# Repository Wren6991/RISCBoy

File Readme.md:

RISCBoy
=======

RISCBoy is an open-source portable games console, designed from scratch. This includes:

- A RISC-V compatible CPU
- A raster graphics pipeline and display controller
- Other chip infrastructure: busfabric, memory controllers, UART, GPIO etc.
- A PCB layout in KiCad

It is a Gameboy Advance from a parallel universe where RISC-V existed in 2001. A love letter to the handheld consoles from my childhood, and a 3AM drunk text to the technology that powered them.

The design is written in synthesisable Verilog 2005, and is intended to fit onto an iCE40-HX8k FPGA. This is a LUT4-based FPGA with 7680 logic elements, so fitting a 32 bit games console requires a crowbar and some vaseline, or perhaps just careful design. The HX8k was once the largest FPGA targeted by the open-source [Icestorm](http://www.clifford.at/icestorm/) FPGA toolchain, but that toolchain has since [moved on](https://github.com/SymbiFlow/prjtrellis) to [greater things](https://github.com/SymbiFlow/prjxray).

More detailed information can be found in the [documentation](doc/riscboy_doc.pdf).

The processor supports the RV32IMC instruction set, and passes the RISC-V compliance suite for these instructions, as well as the [riscv-formal](https://github.com/SymbioticEDA/riscv-formal) verification suite, and some of my own formal property checks for instruction frontend consistency and basic bus compliance. It also supports M-mode CSRs, exceptions, and a simple compliant extension for vectored external interrupts.

Cloning
-------

**This repository uses submodules for HDL as well as tests**

```bash
git clone --recursive https://github.com/Wren6991/RISCBoy.git riscboy
```

Alternatively

```bash
git clone https://github.com/Wren6991/RISCBoy.git riscboy
cd riscboy
git submodule update --init --recursive
```

Note a recursive submodule update is required to run the processor's standalone tests. This is not necessary for building RISCBoy gateware.

Building RV32IMC Toolchain
-------------------------

The RV32IMC toolchain is required for compilation of software-based tests. Follow the instructions on the [RISC-V GNU Toolchain GitHub](https://github.com/riscv/riscv-gnu-toolchain), except for the configure line:

```bash
# Prerequisites for Ubuntu 20.04
sudo apt install -y autoconf automake autotools-dev curl python3 libmpc-dev libmpfr-dev libgmp-dev gawk build-essential bison flex texinfo gperf libtool patchutils bc zlib1g-dev libexpat-dev
cd /tmp
git clone --recursive https://github.com/riscv/riscv-gnu-toolchain
cd riscv-gnu-toolchain
# The ./configure arguments are the most important difference
./configure --prefix=/opt/riscv --with-arch=rv32imc --with-abi=ilp32 --with-multilib-generator="rv32i-ilp32--;rv32ic-ilp32--;rv32im-ilp32--;rv32imc-ilp32--"
sudo mkdir /opt/riscv
sudo chown $(whoami) /opt/riscv
make -j $(nproc)
```

On smaller FPGAs, like the iCE40 UP5k, RISCBoy may be configured to use a smaller RV32I variant of the processor, rather than the higher-performance RV32IMC version. The compiler will support any of the ISA variants available on RISCBoy, but we must also instruct the toolchain build scripts to produce standard libraries for these variants, via the `--with-multilib` arguments. Running a RV32I executable linked against an RV32IMC standard library on an RV32I-only processor will ruin your day!

Simulation
----------

The simulation flow is driven by Xilinx ISIM 14.x; makefiles are found in the scripts/ folder. This has only been tested with the Linux version of ISIM.

You will also need to checkout the RISC-V compliance suite in order to run these tests (note the `-- test` is required to stop git from looking in the KiCad directories and complaining about the library structure there).

```
$ git submodule update --init --recursive
```

Once this is ready, you should be able to run the following:

```bash
. sourceme
cd test
./runtests
```

which will run all of the HDL-level tests. Software tests will require the RV32IC toolchain. You may need to adjust some of the paths in `sourceme` if ISIM is installed in a non-default location. To graphically debug a test, run its makefile directly:

```bash
cd system
make TEST=helloworld gui
```

PCB
---

The image shows the Rev A PCB. It is compatible with iTead's 4-layer 5x5 cm prototyping service, which currently costs $65 for 10 boards.

The schematic can be viewed [here (pdf)](board/fpgaboy.pdf)

Rev B will look quite different; I am waiting for the gateware and bootloader to mature before proceeding. My current dev hardware looks a lot like my [Snowflake FPGA board](https://github.com/Wren6991/Snowflake-FPGA).

Synthesis
---------

FPGA synthesis for iCE40 uses an open-source toolchain. If you would like to build this project using the existing makefiles, you will first need to build the toolchain I used:

- [Yosys](https://github.com/yosyshq/yosys) for synthesis
- [nextpnr](https://github.com/YosysHQ/nextpnr) for place and route
- [Project Icestorm](http://www.clifford.at/icestorm/) for bitstream generation

Note that I have only built these on Linux. I've heard it is possible to build these on Windows, but haven't tried it. However, they can be built on a Raspberry Pi, which is neat.

Once the toolchain is in place, run

```bash
. sourceme
cd synth
make -f HX8k-EVN.mk bit
```

to generate an FPGA image suitable for Lattice HX8k evaluation board.

There is also highly experimental support (i.e. not my main dev platform) for ECP5, with board files for the Lattice LEF5UM5G-85F-EVN evaluation board:

```bash
make -f ECP5-EVN.mk BUILD=full bit
```

This build replaces the external, 512 kiB, 16 bit wide SRAM of RISCBoy development hardware with an internal, 256 kiB, 32 bit wide synchronous memory, which Trellis builds out of ECP5 sysmem blocks.

Directory Structure
-------------------

- `board`: KiCad files for main RISCBoy PCB and other small boards used during development
- `doc`: LaTeX source and diagrams for documentation, and the most recently built PDF
- `hdl`: The Verilog source for RISCBoy gateware.
	- `busfabric`: AHB-lite crossbar and APB peripheral fabric
	- `graphics`: Source for the pixel processing unit
	- `hazard5`: Source for the RISC-V processor. This is completely self-contained.
	- `mem`: Memory controllers, and inference/injection wrappers and models for the memories themselves
	- `peris`: Small peripherals such as UART, SPI, PWM
	- `riscboy_core`: Structural module to instantiate and connect the components that comprise RISCBoy
	- `riscboy_fpga`: Top-level wrappers for a few different FPGAs and boards: connect up IOs, provide clock and reset
- `reference`: a few PDFs for standards used in RISCBoy, e.g. the RISC-V instruction set
- `scripts`: Junk that I can't put anywhere else
- `software`: Loose collection of C files that are used for system-level tests. Not really a useful software tree yet.
- `synth`: Working directory for running whole-system synthesis. Top-level makefiles, pin constraint files.
- `test`: Regression tests. Some are Verilog testbenches, others are software testcases that run on simulations of the processor or the full system.

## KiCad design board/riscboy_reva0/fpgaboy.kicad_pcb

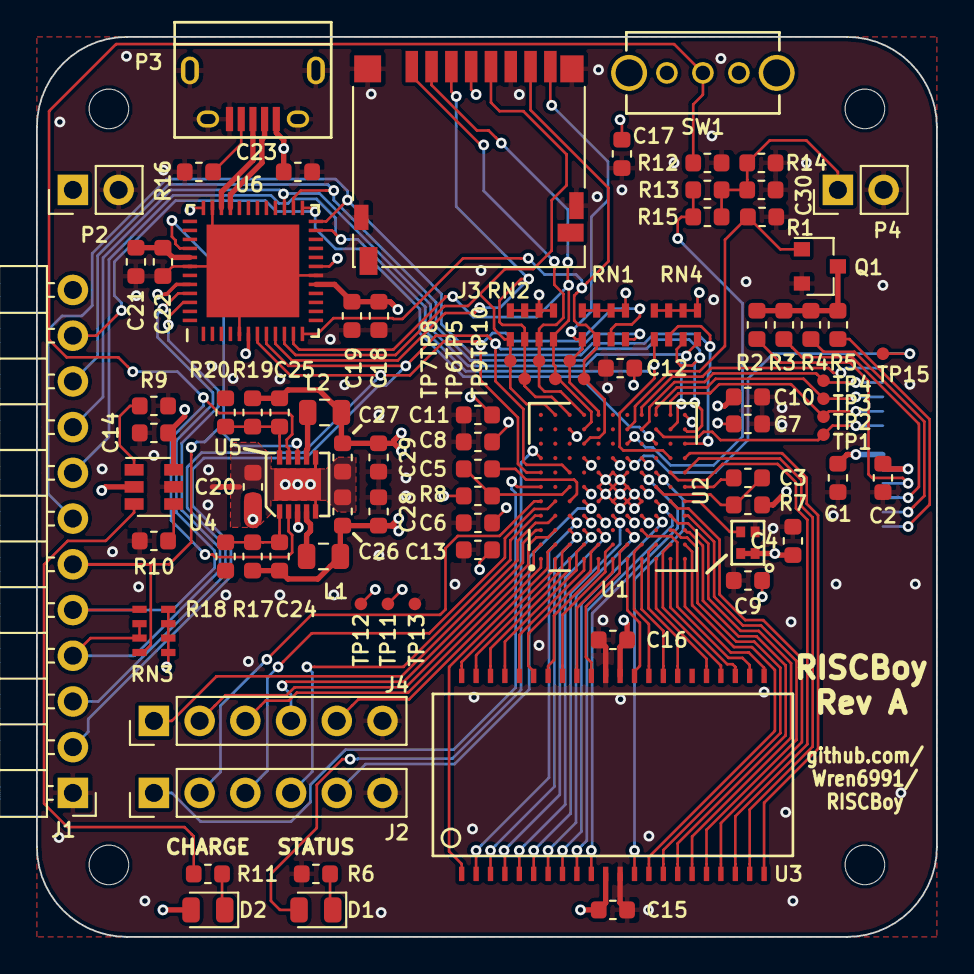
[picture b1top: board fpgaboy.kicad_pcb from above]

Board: 4 copper layers, 50.0 x 50.0 mm, 89 parts (1 on the bottom side), 105 nets.

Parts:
C1, C2, C3, C5, C14, C15, C18, C20, C21, C28, C29: 1u; C_0603_1608Metric
C4, C6, C7, C8, C9, C10, C11, C12, C13, C16, C17, C19, C22, C30: 0.1u; C_0603_1608Metric
C23, C26, C27: 10u; C_0603_1608Metric
C24, C25: 18p; C_0603_1608Metric
D1, D2: LED; LED_0805_2012Metric
J1: Conn_01x12; PinHeader_1x12_P2.54mm_Horizontal
J2, J4: Conn_01x06; PinHeader_1x06_P2.54mm_Vertical
J3: Micro_SD_Card_Det; microSD_HC_Hirose_DM3D-SF
L1, L2: 2u2; R_0805_2012Metric
P1: ILI9341; FFC_18_0.8mm_solder
P2, P4: CONN_01X02; PinHeader_1x02_P2.54mm_Vertical
P3: USB_OTG; USB_Micro-B
Q1: BSS816NW; SOT-23
R1, R9, R12: 10k; R_0603_1608Metric
R2, R3, R4, R5, R14: 220; R_0603_1608Metric
R6, R10, R11, R13, R15: 680; R_0603_1608Metric
R7, R8: 10; R_0603_1608Metric
R16: NF; R_0603_1608Metric
R17: 450k; R_0603_1608Metric
R18, R19, R20: 100k; R_0603_1608Metric
RN1, RN2, RN3, RN4: 10k; RN4-1206
SW1: SWITCH_SPST; SPDT_SLIDE_SWITCH
TP1, TP2, TP3, TP4, TP5, TP6, TP7, TP8, TP9, TP10, TP11, TP12, TP13, TP15: TestPoint; Testpoint_d0.7mm
TP14: Tie_point; tiepoint-0.5
U1: iCE40-HX8k-BG121; BGA-121_11x11_9.0x9.0mm
U2: DSC60XX; LGA4_1.6x1.2mm
U3: GS74116AGP/; TSOP_II_44
U4: BQ21040; SOT-23-6
U5: NCP1532; UDFN-10
U6: SAML22G18A; QFN-48_EP_7x7_Pitch0.5mm

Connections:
+1V2: C7.1, C9.1, C11.1, C13.1, C25.1, C27.1, C29.1, L2.2, R7.2, R8.2, R19.1, TP11.1, U1.D4, U1.D8, U1.H4, U1.H8
+3V3: C1.1, C4.1, C6.1, C8.1, C10.1, C12.1, C15.1, C16.1, C17.1, C18.1, C19.1, C24.1, C26.1, C28.1, J3.4, L1.2, P1.9, R17.1, RN1.5, RN1.6, RN1.7, RN1.8, RN2.5, RN2.6, RN2.7, RN2.8, RN3.5, RN3.6, RN3.7, RN3.8, RN4.5, RN4.6, RN4.7, RN4.8, TP12.1, U1.C10, U1.D6, U1.E4, U1.F8, U1.G4, U1.H6, U1.L11, U2.1, U2.4, U3.11, U3.33, U6.6, U6.17, U6.19, U6.36, U6.44
+5V: C14.1, C23.1, P3.1, U4.6
+BATT: C2.1, C20.1, D2.2, J1.12, P1.10, P2.1, SW1.1, U4.2, U5.3
/AUDIO_PWM: R13.1, R15.1, U1.G9
/CHARGE: R11.2, U4.3
/CLK_OSC: U1.L5, U2.3
/FPGA_CFG_DONE: J1.8, RN4.1, U1.K8, U6.23
/FPGA_CFG_SCK: J1.10, RN4.3, U1.L10, U6.26
/FPGA_CFG_SI: J1.11, U1.J9, U6.25
/FPGA_CFG_~RST: J1.7, RN4.2, U1.L9, U6.24
/FPGA_CFG_~SS: J1.9, RN4.4, U1.K10, U6.27
/FPGA_HEARTBEAT: D1.2, U1.A8
/FPGA_UART_RX: J1.2, RN1.4, U1.C7, U6.8
/FPGA_UART_TX: J1.3, RN1.3, U1.A7, U6.7
/GPIO_SW0: J2.1, U1.A6
/GPIO_SW1: J2.2, U1.A5
/GPIO_SW2: J2.3, U1.B5
/GPIO_SW3: J2.4, U1.A4
/GPIO_SW4: J2.5, U1.D5
/GPIO_SW5: J4.1, U1.B4
/GPIO_SW6: J4.2, U1.B3
/GPIO_SW7: J4.3, U1.A2
/GPIO_SW8: J4.4, U1.A3
/GPIO_SW9: J4.5, U1.A1
/LCD_CS: P1.5, TP3.1, U1.J11
/LCD_D~C~: P1.6, TP2.1, U1.K11
/LCD_PWM: Q1.1, R1.1, U1.G10
/LCD_RESET: P1.2, TP15.1, U1.G8
/LCD_SCL: P1.7, TP1.1, U1.J10
/LCD_SDA: P1.4, TP4.1, U1.H10
/LCD_SDO: P1.3, U1.H11
/SRAM_A0: U1.E3, U3.5
/SRAM_A1: U1.D3, U3.4
/SRAM_A2: U1.C3, U3.3
/SRAM_A3: U1.C4, U3.2
/SRAM_A4: U1.B2, U3.1
/SRAM_A5: U1.B1, U3.44
/SRAM_A6: U1.C2, U3.43
/SRAM_A7: U1.C1, U3.42
/SRAM_A8: U1.J1, U3.27
/SRAM_A9: U1.K2, U3.26
/SRAM_A10: U1.K1, U3.25
/SRAM_A11: U1.H3, U3.24
/SRAM_A12: U1.L7, U3.21
/SRAM_A13: U1.K7, U3.20
/SRAM_A14: U1.K5, U3.19
/SRAM_A15: U1.L4, U3.18
/SRAM_A16: U1.L8, U3.22
/SRAM_A17: U1.L1, U3.23
/SRAM_DQ1: U1.G3, U3.7
/SRAM_DQ2: U1.J4, U3.8
/SRAM_DQ3: U1.J5, U3.9
/SRAM_DQ4: U1.H7, U3.10
/SRAM_DQ5: U1.J7, U3.13
/SRAM_DQ6: U1.L2, U3.14
/SRAM_DQ7: U1.K3, U3.15
/SRAM_DQ8: U1.L3, U3.16
/SRAM_DQ9: U1.J2, U3.29
/SRAM_DQ10: U1.H1, U3.30
/SRAM_DQ11: U1.H2, U3.31
/SRAM_DQ12: U1.G1, U3.32
/SRAM_DQ13: U1.G2, U3.35
/SRAM_DQ14: U1.F1, U3.36
/SRAM_DQ15: U1.F2, U3.37
/SRAM_DQ16: U1.E1, U3.38
/SRAM_~CE: U1.F4, U3.6
/SRAM_~LB: U1.E2, U3.39
/SRAM_~OE: U1.D2, U3.41
/SRAM_~UB: U1.D1, U3.40
/SRAM_~WE: U1.K4, U3.17
/USB_DM: P3.2, U6.33
/USB_DP: P3.3, U6.34
/VCCPLL0: C3.1, R7.1, U1.J6
/VCCPLL1: C5.1, R8.1, U1.C6
/VDDCORE: C21.1, C22.1, U6.41
/uC_SWCLK: J1.5, RN3.1, U6.45
/uC_SWD: J1.4, RN3.2, RN3.3, U6.46
/uC_~RST: J1.6, RN3.4, U5.8, U6.40
/uSD_CLK: J3.5, RN2.1, TP8.1, U1.B11, U6.10
/uSD_CMD: J3.3, RN2.2, TP7.1, U1.C11, U6.9
/uSD_DAT0: J3.7, RN1.2, TP9.1, U1.D9, U6.12
/uSD_DAT1: J3.8, RN1.1, TP10.1, U1.E11
/uSD_DAT2: J3.1, RN2.3, TP5.1, U1.D11
/uSD_DAT3: J3.2, RN2.4, TP6.1, U1.D10, U6.11
GND: C1.2, C2.2, C4.2, C6.2, C7.2, C8.2, C9.2, C10.2, C11.2, C12.2, C13.2, C14.2, C15.2, C16.2, C17.2, C18.2, C19.2, C21.2, C22.2, C23.2, C28.2, C29.2, C30.2, J1.1, J2.6, J3.6, J3.11, J4.6, P1.1, P1.8, P2.2, P3.5, P3.6, P4.2, Q1.2, R1.2, R6.2, R9.2, R10.2, R12.2, R14.2, R16.2, R18.2, R20.2, TP13.1, TP14.1, U1.E5, U1.E6, U1.E7, U1.F5, U1.F6, U1.F7, U1.G5, U1.G6, U1.G7, U1.H5, U2.2, U3.12, U3.34, U4.5, U6.5, U6.18, U6.35, U6.42, U6.49
GNDPWR: C20.2, C26.2, C27.2, TP14.2, U5.5, U5.6
unnamed: C3.2, U1.L6
unnamed: C5.2, U1.C5
unnamed: C24.2, R17.2, R18.1, U5.1
unnamed: C25.2, R19.2, R20.1, U5.10
unnamed: C30.1, P4.1, R13.2, R14.1, R15.2
unnamed: D1.1, R6.1
unnamed: D2.1, R11.1
unnamed: L1.1, U5.4
unnamed: L2.1, U5.7
unnamed: P1.11, R2.1
unnamed: P1.12, R3.1
unnamed: P1.13, R4.1
unnamed: P1.14, R5.1
unnamed: P3.4, R16.1
unnamed: Q1.3, R2.2, R3.2, R4.2, R5.2
unnamed: R9.1, U4.1
unnamed: R10.1, U4.4
unnamed: R12.1, SW1.2, U5.2, U5.9

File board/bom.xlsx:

Ref | Val | Type
C10 | 0.1u | C
C11 | 0.1u | C
C12 | 0.1u | C
C13 | 0.1u | C
C16 | 0.1u | C
C17 | 0.1u | C
C19 | 0.1u | C
C22 | 0.1u | C
C30 | 0.1u | C
C4 | 0.1u | C
C6 | 0.1u | C
C7 | 0.1u | C
C8 | 0.1u | C
C9 | 0.1u | C
C23 | 10u | C
C26 | 10u | C
C27 | 10u | C
C24 | 18p | C
C25 | 18p | C
C1 | 1u | C
C14 | 1u | C
C15 | 1u | C
C18 | 1u | C
C2 | 1u | C
C20 | 1u | C
C21 | 1u | C
C28 | 1u | C
C29 | 1u | C
C3 | 1u | C
C5 | 1u | C
D1 | LED | D
D2 | LED | D
J2 | Conn_01x06 | J
J4 | Conn_01x06 | J
J1 | Conn_01x12 | J
J3 | Micro_SD_Card_Det | J
L1 | 2u2 | L
L2 | 2u2 | L
P2 | CONN_01X02 | P
P4 | CONN_01X02 | P
P1 | ILI9341 | P
P3 | USB_OTG | P
Q1 | BSS816NW | Q
R7 | 10 | R
R8 | 10 | R
R14 | 220 | R
R2 | 220 | R
R3 | 220 | R
R4 | 220 | R
R5 | 220 | R
R10 | 680 | R
R11 | 680 | R
R13 | 680 | R
R15 | 680 | R
R6 | 680 | R
R18 | 100k | R
R19 | 100k | R
R20 | 100k | R
R1 | 10k | R
R12 | 10k | R
R9 | 10k | R
RN1 | 10k | R
RN2 | 10k | R
RN3 | 10k | R
RN4 | 10k | R
R17 | 450k | R
R16 | NF | R
SW1 | SWITCH_SPST | S
U4 | BQ21040 | U
U2 | DSC60XX | U
U3 | GS74116AGP/ | U
U1 | iCE40-HX8k-BG121 | U
U5 | NCP1532 | U
U6 | SAML22G18A | U

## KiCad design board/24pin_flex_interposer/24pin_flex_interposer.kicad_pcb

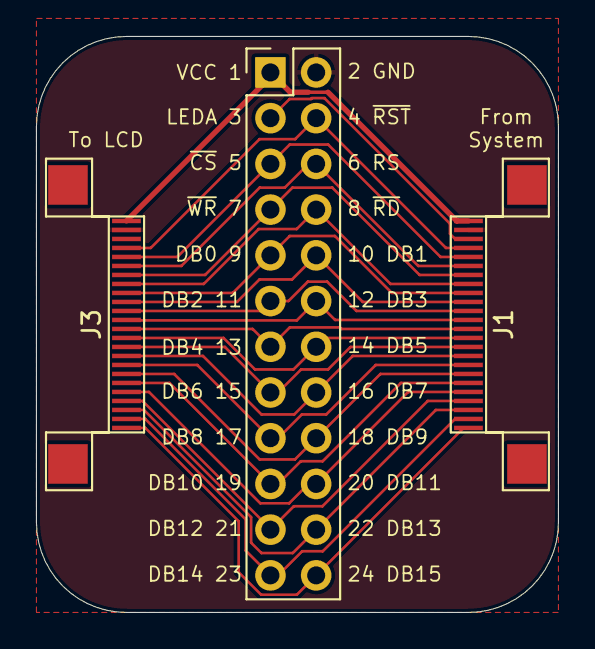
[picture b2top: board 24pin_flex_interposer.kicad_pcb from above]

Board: 2 copper layers, 29.0 x 32.0 mm, 3 parts (0 on the bottom side), 24 nets.

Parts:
J1, J3: TF31-24S-0.5SH; FPC_24
J2: Conn_02x12_Odd_Even; PinHeader_2x12_P2.54mm_Vertical

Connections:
/LCD1: J1.24, J2.1, J3.1
/LCD2: J1.23, J2.2, J3.2
/LCD3: J1.22, J2.3, J3.3
/LCD4: J1.21, J2.4, J3.4
/LCD5: J1.20, J2.5, J3.5
/LCD6: J1.19, J2.6, J3.6
/LCD7: J1.18, J2.7, J3.7
/LCD8: J1.17, J2.8, J3.8
/LCD9: J1.16, J2.9, J3.9
/LCD10: J1.15, J2.10, J3.10
/LCD11: J1.14, J2.11, J3.11
/LCD12: J1.13, J2.12, J3.12
/LCD13: J1.12, J2.13, J3.13
/LCD14: J1.11, J2.14, J3.14
/LCD15: J1.10, J2.15, J3.15
/LCD16: J1.9, J2.16, J3.16
/LCD17: J1.8, J2.17, J3.17
/LCD18: J1.7, J2.18, J3.18
/LCD19: J1.6, J2.19, J3.19
/LCD20: J1.5, J2.20, J3.20
/LCD21: J1.4, J2.21, J3.21
/LCD22: J1.3, J2.22, J3.22
/LCD23: J1.2, J2.23, J3.23
/LCD24: J1.1, J2.24, J3.24

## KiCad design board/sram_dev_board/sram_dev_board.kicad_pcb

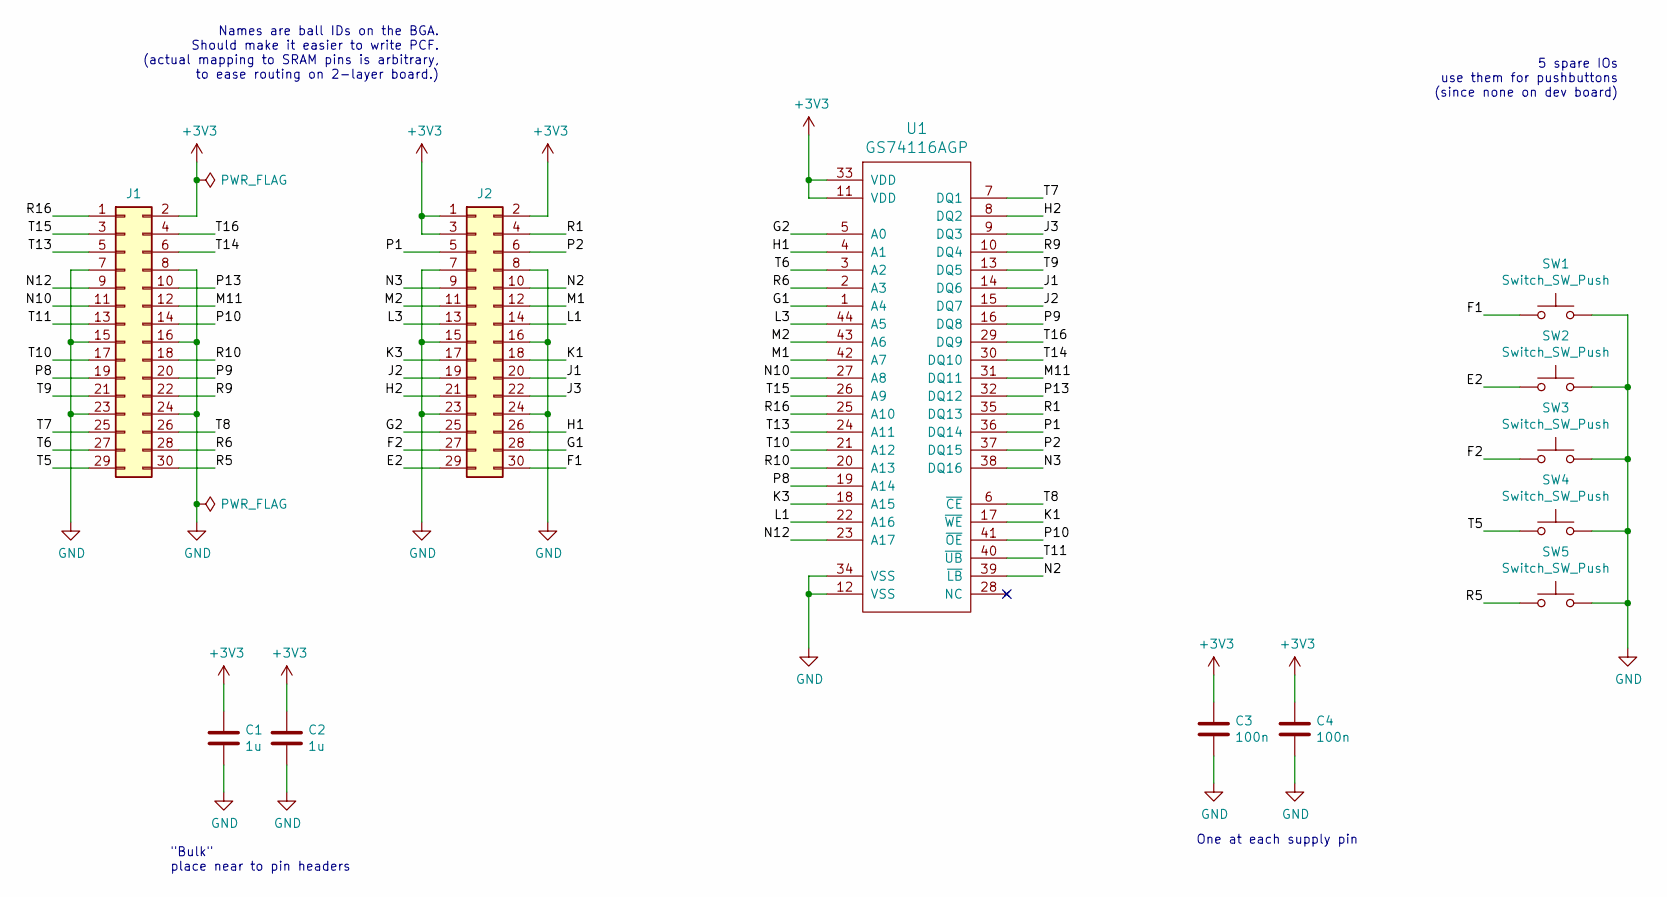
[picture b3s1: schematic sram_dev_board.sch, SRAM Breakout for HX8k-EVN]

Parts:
C1, C2: 1u; C_0603_1608Metric_Pad1.05x0.95mm_HandSolder
C3, C4: 100n; C_0603_1608Metric_Pad1.05x0.95mm_HandSolder
J1, J2: Conn_02x15_Odd_Even; PinHeader_2x15_P2.54mm_Vertical
SW1, SW2, SW3, SW4, SW5: Switch_SW_Push; SW_SPST_EVQP0
U1: GS74116AGP; TSOP_II_44

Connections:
+3V3: C1.1, C2.1, C3.1, C4.1, J1.2, J2.1, J2.2, J2.3, U1.11 (VDD), U1.33 (VDD)
/E2: J2.29, SW2.1
/F1: J2.30, SW1.1
/F2: J2.27, SW3.1
/G1: J2.28, U1.1 (A4)
/G2: J2.25, U1.5 (A0)
/H1: J2.26, U1.4 (A1)
/H2: J2.21, U1.8 (DQ2)
/J1: J2.20, U1.14 (DQ6)
/J2: J2.19, U1.15 (DQ7)
/J3: J2.22, U1.9 (DQ3)
/K1: J2.18, U1.17 (~WE)
/K3: J2.17, U1.18 (A15)
/L1: J2.14, U1.22 (A16)
/L3: J2.13, U1.44 (A5)
/M1: J2.12, U1.42 (A7)
/M2: J2.11, U1.43 (A6)
/M11: J1.12, U1.31 (DQ11)
/N2: J2.10, U1.39 (~LB)
/N3: J2.9, U1.38 (DQ16)
/N10: J1.11, U1.27 (A8)
/N12: J1.9, U1.23 (A17)
/P1: J2.5, U1.36 (DQ14)
/P2: J2.6, U1.37 (DQ15)
/P8: J1.19, U1.19 (A14)
/P9: J1.20, U1.16 (DQ8)
/P10: J1.14, U1.41 (~OE)
/P13: J1.10, U1.32 (DQ12)
/R1: J2.4, U1.35 (DQ13)
/R5: J1.30, SW5.1
/R6: J1.28, U1.2 (A3)
/R9: J1.22, U1.10 (DQ4)
/R10: J1.18, U1.20 (A13)
/R16: J1.1, U1.25 (A10)
/T5: J1.29, SW4.1
/T6: J1.27, U1.3 (A2)
/T7: J1.25, U1.7 (DQ1)
/T8: J1.26, U1.6 (~CE)
/T9: J1.21, U1.13 (DQ5)
/T10: J1.17, U1.21 (A12)
/T11: J1.13, U1.40 (~UB)
/T13: J1.5, U1.24 (A11)
/T14: J1.6, U1.30 (DQ10)
/T15: J1.3, U1.26 (A9)
/T16: J1.4, U1.29 (DQ9)
GND: C1.2, C2.2, C3.2, C4.2, J1.7, J1.8, J1.15, J1.16, J1.23, J1.24, J2.7, J2.8, J2.15, J2.16, J2.23, J2.24, SW1.2, SW2.2, SW3.2, SW4.2, SW5.2, U1.12 (VSS), U1.34 (VSS)

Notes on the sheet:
One at each supply pin
"Bulk" place near to pin headers
Names are ball IDs on the BGA. Should make it easier to write PCF. (actual mapping to SRAM pins is arbitrary, to ease routing on 2-layer board.)
5 spare IOs use them for pushbuttons (since none on dev board)

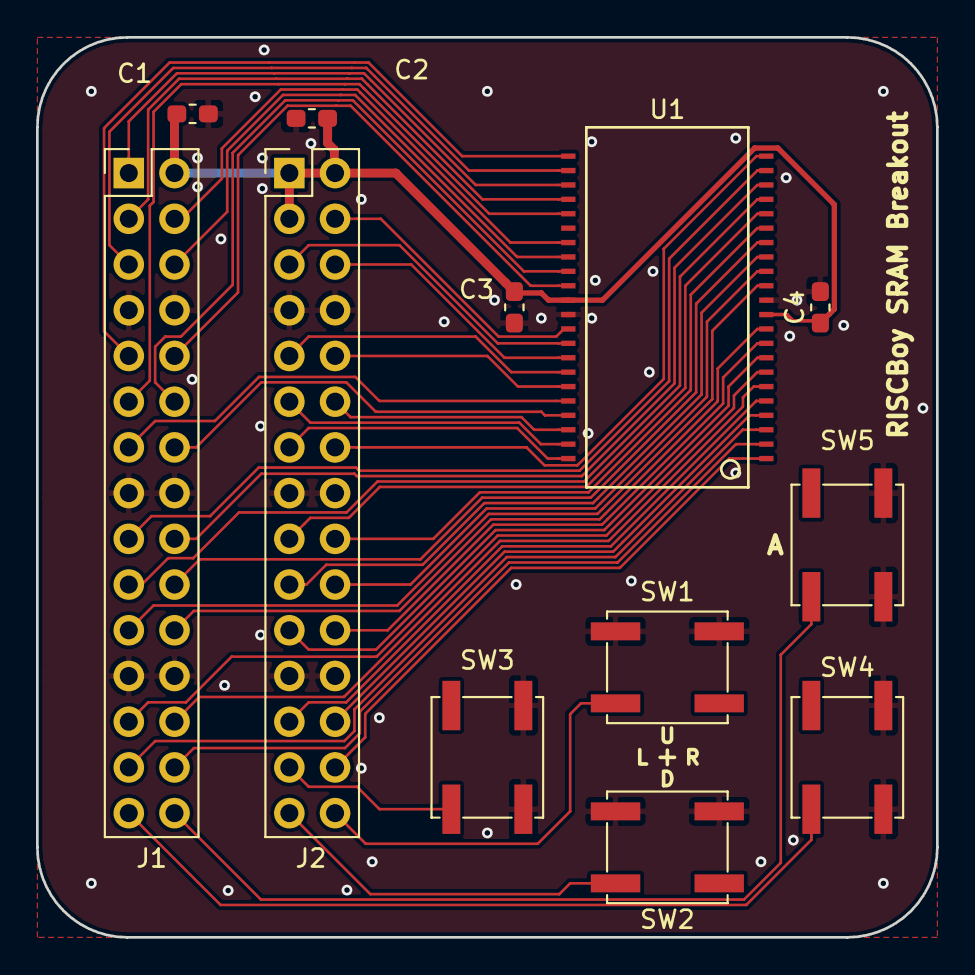
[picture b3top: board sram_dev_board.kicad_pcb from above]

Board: 2 copper layers, 50.0 x 50.0 mm, 12 parts (0 on the bottom side), 46 nets.

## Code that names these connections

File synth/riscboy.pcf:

# Generated with extract_ref_nets

set_io audio_pwm            G9
set_io clk_osc              L5
set_io fpga_heartbeat       A8
set_io fpga_uart_rx         C7
set_io fpga_uart_tx         A7
set_io gpio_sw[0]           A6
set_io gpio_sw[1]           A5
set_io gpio_sw[2]           B5
set_io gpio_sw[3]           A4
set_io gpio_sw[4]           D5
set_io gpio_sw[5]           B4
set_io gpio_sw[6]           B3
set_io gpio_sw[7]           A2
set_io gpio_sw[8]           A3
set_io gpio_sw[9]           A1
set_io lcd_cs               J11
set_io lcd_dc               K11
set_io lcd_pwm              G10
set_io lcd_reset            G8
set_io lcd_scl              J10
set_io lcd_sda              H10
set_io lcd_sdo              H11
set_io sram_a[0]            E3
set_io sram_a[1]            D3
set_io sram_a[2]            C3
set_io sram_a[3]            C4
set_io sram_a[4]            B2
set_io sram_a[5]            B1
set_io sram_a[6]            C2
set_io sram_a[7]            C1
set_io sram_a[8]            J1
set_io sram_a[9]            K2
set_io sram_a[10]           K1
set_io sram_a[11]           H3
set_io sram_a[12]           L7
set_io sram_a[13]           K7
set_io sram_a[14]           K5
set_io sram_a[15]           L4
set_io sram_a[16]           L8
set_io sram_a[17]           L1
set_io sram_dq[0]           G3
set_io sram_dq[1]           J4
set_io sram_dq[2]           J5
set_io sram_dq[3]           H7
set_io sram_dq[4]           J7
set_io sram_dq[5]           L2
set_io sram_dq[6]           K3
set_io sram_dq[7]           L3
set_io sram_dq[8]           J2
set_io sram_dq[9]          H1
set_io sram_dq[10]          H2
set_io sram_dq[11]          G1
set_io sram_dq[12]          G2
set_io sram_dq[13]          F1
set_io sram_dq[14]          F2
set_io sram_dq[15]          E1
set_io sram_ce              F4
set_io sram_lb              E2
set_io sram_oe              D2
set_io sram_ub              D1
set_io sram_we              K4
set_io usd_clk              B11
set_io usd_cmd              C11
set_io usd_dat[0]           D9
set_io usd_dat[1]           E11
set_io usd_dat[2]           D11
set_io usd_dat[3]           D10

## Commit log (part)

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2019-07-11 Fix basename vs notdir in system tb makefile
2019-07-12 First real attempt at multiply/divide/modulo circuit
2019-07-13 Add optional counter registers to CSRs
2019-07-16 Further savings in muldiv_seq: replace add/sub with an add, and instead calculate negative abs(b) rather than abs(b), if performing division.
2019-07-16 Fix silly bugs in CSR access, and add CSR compliance tests to regressions
2019-07-17 Update to latest version of RISC-V compliance suite
2019-07-18 Add trap vector table layout to documentation
2019-07-19 Add default vector table to init.S
2019-07-20 Bugs related to traps/IRQs: bubbling the trapped instruction on the way from X to M, interrupt decode and masking, making sure register specifiers are clear for the exception-generating instructions.
2019-07-21 Connect UART IRQ, add simple UART IRQ testcase
2019-07-21 Add optional bus monitoring to system tb
2019-07-21 Add simple IRQ forcing (tbman), add IRQ priority test where all IRQs are raised at once, and order of service is checked.
2019-09-09 Add handle_misaligned_loadstore to regressions
2019-09-10 Reorganise CDC and rewrite async FIFO
2019-09-11 Add sync FIFO to SPI .f file
2019-09-13 Plausible attempt at wiring in the LCD hardware.
2019-09-15 First pass at PPU blender and raster counter RTL
2019-11-16 Add pixel gearbox RTL
2019-12-16 Tidy up naming of PPU modules
2019-12-17 Extend smoke test to render a simple 64x64 pixel playfield. Shake some obvious bugs out. Add this test to regressions
2019-12-18 First pass at a bus master/arbiter for PPU
2019-12-18 Wire background, blend, raster counter and busmaster into PPU. Add some BG config to PPU regs.
2019-12-18 Run system regressions from main memory instead of boot RAM (need more space)
2019-12-18 Fix hprot typo in ahbl_crossbar
2019-12-19 Nicer scrolling tartan for the LCD :)
2019-12-19 Simplify BG address generation by changing tileset layout
2019-12-19 Correct landscape orientation for ILI9341
2019-12-19 Appease the ILI9341 gods with a MADCTL before the sw reset (otherwise display requires two inits to properly initialise after a hard LCD power cycle)
2019-12-20 Speculative fix for issue in ppu bg when pixels per fetch is greater than tile size
2019-12-20 Add zelda graphics demo
2019-12-21 Add transparency and palette mapping to PPU. First pass, but nothing else seems broken.
2019-12-22 Fix shift size and bit expansion for ARGB1232
2019-12-22 Update mini tile demo to use paletted colour
2019-12-23 Add a second background to PPU, and add a simple parallax scroll demo. Seem to be some kinks in the asset pipeline that need working out
2019-12-25 Fix use of SystemVerilog priority keyword as port name in onehot_priority_dynamic
2019-12-26 Add wstrobe to regblock, and use it for PPU BG flush signal
2019-12-27 Add sprite config to PPU regs, and factor out pixel streaming from backgrounds
2019-12-28 Remove defunct diagrams
2019-12-28 Add WO access type to regblock. Save 230 LUTs from PPU by making most sprite and background config read only.
2019-12-29 Fix typo in sprite fetch address gen -- first working sprite on screen! Fix reversed priority of sprites/backgrounds, and also reverse so that higher BGs win
2019-12-29 Make more verilog tools believe that the blender input hookup can be resolved at elaboration time. Add ADDR_MASK parameter to PPU, which can save a few LUTs by trimming address bits.
2019-12-30 Make size of screen coords distinct from playfield coords. Shrink screen coord size by 1 bit.
2019-12-31 Remove memory dump module from riscboy_core, which has not been used for a long time
2020-01-01 Add simple sprite test case -- walk through all positions of sprite relative to +-x screen edges
2020-01-02 Pixel streamer: no early-out on seeking logic. Saves a couple of LUTs, but can increase seek time.
2020-01-02 Provide a more helpul synth cmdline in Readme
2020-01-02 Backgrounds: recalculate U, V on every cycle, to avoid local state and counter.
2020-01-03 Speculative fix for 8 pixel sprite beam intersection
2020-01-03 Optimise sprite X intersection in sprite AGU, save 15 LUTs or so
2020-01-03 Squeeze some LUTs out of the UART: reduce fractional divisor to 4 bits, and make divisor write-only
2020-01-03 Don't sync the full width of the LCD shifter shift count between clock domains
2020-01-04 Add more platformer art assets from opengameart
2020-01-04 Hack for paletted transparency in packtiles
2020-01-05 Reduce PPU internal data width from 32 to 16. This reduces HX8k utilisation from 96% to 91%.
2020-01-07 Commit ECP5 synth experiment
2020-01-08 Add simple test for PPU poker
2020-01-09 Eliminate wasted cycle when entering wait state, and save some logic in poker
2020-01-11 Poker: replace JUMP with BCEQ/BCNE
2020-02-16 PPU: specify size of X and Y screen coordinates separately, allows small area savings
2020-02-16 Poker codegen functions: return size rather than incrementing pointer directly
2020-02-17 Rebase of clutter from desktop
2020-02-20 Fix parallax demo slowly scrolling up :)
2020-02-26 Add RV32IM tests to regressions. Disable M extension for riscboy builds as we don't have space.
2020-02-28 Don't commit operands to muliplier when X is in RAW stall against M
2020-03-01 Use correct macro for riscv-formal bus fairness constraint
2020-03-01 hazard5_decode: fix case where flush is asserted while X is stalled.
2020-03-02 hazard5_rvfi_monitor: clarify that CSR access faults are traps. Requires a debug wire :(
2020-03-03 Fix false positive CIR lock when m_jump_req and d_jump_req asserted simultaneously, causing D PC to be trashed
2020-03-04 Add formal check for multiply/divide/modulo circuit
2020-03-08 Add first draft doc for new PPU architecture
2020-03-10 More spec work on new PPU
2020-03-11 Add affine coordinate generator for ppu2
2020-03-13 Sketch in PPU command proc, blender, pixel unpack. Good enough shape that nothing else seems broken by this.
2020-03-13 Correct typo in affine coordinate generator, wrong b fractional bits
2020-03-14 Fix cproc not capturing blit skip signal correctly. Fix inverted bounds check in pixel agu (oops). Fix some broken handshaking.
2020-03-15 Add spinning wilber demo
2020-03-15 Add PPU header changes for spin demo
2020-03-15 Add video script for unassuming link name
2020-03-16 Add loading of hot code to internal RAM
2020-03-17 Make UART RTS level configurable via parameter, and set it so that Rickroll runs nicely
2020-03-18 Packtiles: always output a full-sized palette, even when fewer colours are present (zero-pad)
2020-03-18 Commit files from 'Project Unassuming Link Name'
2020-03-18 Extend UART loopback test to slightly cover the RTS/CTS logic
2020-03-18 Add app dir for fill_triangle_test
2020-03-19 Use iCE40UP5k SPRAMs for 128k main memory on iCEBreaker
2020-03-20 Push address masking further pack through the PPU, to avoid the huge amount of logic contributing to the MSB
2020-03-22 Fix a number of minor bugs in tilemapping logic, and port forward old ppu_smoke tile test.
2020-03-22 Couple of minor HDL snags, non-critical
2020-04-13 Port Zelda tile demo, with affine camera
2020-05-10 First pass at separating PPU from display controller. At a point where hello world runs again.
2020-05-11 Add DVI output to ULX3S port (and optionally to others)
2020-08-23 Fix up some tests broken during manic lockdown work
2020-08-25 Dockerfile for automatic builds, and to ensure that users do not have to spend too much time on the development environment
2020-08-27 Update .gitmodules
    My apologies! I'd meant to make it easier.... and I went and made it impossible. I think we are good to go now.
2020-12-01 Fix port direction on PPU cproc
2020-12-01 Port sprite_demo to PPU2 (seems there might be an off-by-one in sprite vertical size?)
2020-12-02 Fix off-by-one in PPU blit vertical test, and clean up sprite_demo a little
2020-12-02 Add procedure call stack to PPU (replace JUMP with PUSH/POPJ
2020-12-03 ULX3S: add game + reset buttons, set bootloader to 3 Mbaud
2020-12-03 Couple of minor fixes in scripts
2020-12-04 Increase second stage offset for ULX3S build so we can boot from flash
2020-12-06 Add some PPU testcases and beginnings of test scripts
2020-12-07 More PPU testcases
2020-12-07 Remove unnecessary address-phase capture from PPU busmaster
2020-12-09 Add multilib toolchain build to readme, and remove $ signs from bash text
2020-12-12 Make cutdown processor more cutdown (use new REDUCED_BYPASS on hazard5, and disable RVC)
2020-12-12 Remove useless GPIO muxing functionality to save area of config registers
2020-12-14 Remove output controls from GPIOs used only for input
2020-12-14 Fix couple of wiring issues that were making ISIM hit internal asserts
2020-12-14 New FIFO in hazard5 frontend, saves ~55 LCs
2021-01-09 Use smaller SRAM adapter (no write buffer) on icebreaker
2021-01-09 Playing with HDMI on icebreaker. Frequent placement failures.
2021-01-11 Force promotion of clk_bit, and connect clk_bit correctly on riscboy_core
2021-01-11 Move pixel doubling to downstream side of sys->pix FIFO in DVI dispctrl
2021-02-15 Restore original (SPI LCD) icebreaker build
2021-02-15 Move revA0 board stuff into a subdirectory under board/
2021-02-20 More work on revb board schematic
2021-02-21 Add separate audio supply
2021-02-22 Add -s argument to icepack, so a flash power down command is not issued after the bitstream is loaded
2021-02-22 Add power testpoints, connect a few more spare FPGA IOs
2021-02-23 Start generating and assigning footprints for rev B board
2021-03-06 Battery footprint for rev b board
2021-03-13 Start drawing board outline
2021-03-27 Bump libfpga for ahb_cache_readonly, and add simple tb for it
2021-03-29 Add some 0-padding to end of the small asm testcases, hack for X check which is now reachable with dual port processor
2021-10-09 Bump libfpga/hazard5, update writeback cache testbench
2023-06-12 Workaround for AHB arbiter issue which was exposed by update to APB bridge
2023-06-14 Bump scripts: don't attempt to use broken SA placer in iCE40 seed sweeping
2023-06-14 Avoid redefining CLK_SYS_MHZ in blinky
2023-06-14 Remove the following platforms:
    - Upduino
    - DVI on iCEBreaker
    - TinyFPGA BX
    - ECP5 eval board
    These are not maintained and often break. The remaining platforms are:
    - HX8k eval board with serial display
2023-06-14 Fix up tb for new SRAM connection, I still have the old cursed sim setup on my thinkpad
2023-06-16 Make PPU bus interface safe at higher memory latencies by limiting the number of in-flight transfers
2023-06-16 Oops, revert SRAM pipe stage accidentally enabled in SRAM PHY -- not ready for that yet
2023-06-16 Improve PPU bus timing by adding a separate valid bit to the address pipestage
2023-06-16 Use 1R1W memory in SRAM1 to simplify write control path
2023-06-19 Disable load/store alignment check as it costs quite a bit of fmax
2023-06-21 WIP: new SRAM controller. Can run some code from SRAM, but once the PPU is running it eventually falls over
2023-06-22 Add CXXRTL testcase for new SRAM controller, seems to have found a failure mode, will debug tomorrow
2023-06-23 Revert accidental tagging of Hazard5 negedge reg read patch, which is not ready for prime time
2023-06-23 Fix tie-off value on tbio interface
2023-06-23 Fix up demo apps so they all build again
2023-06-24 Bump processor: move instruction decompress from start of stage 2 to end of stage 1
2023-06-24 Update APB bridge for improved HREADY output timing
2023-06-24 Improve PPU bus timing, this seems like a genuine optimisation but weirdly is making system-level timing worse, so put on a branch for now
2023-06-26 Bump hazard5 for frequency optimisations
2023-06-26 Resize PPU buffers for correct SRAM latency
2023-07-01 Enable abc9 flow3 script for better synthesis results
2023-07-03 Simplify span_start logic by precomputing whether clip region is nonempty. (PPU frequency optimisation)
2025-11-22 Hacks for building on GF180MCU.
    Also apparently type is a keyword in SystemVerilog, so that's fun
2025-11-23 Add missing VDD/VSS connection
2025-11-24 Regenerate PPU regblock (change to how w1c is generated to support multi-bit values)
2025-11-25 Back out last change as it makes the detailed router crash
2025-11-27 Regenerate APB regblocks with registered address
2025-11-29 Reduce CPROC_PC register width by 1 bit to match reduced SRAM address width
2025-12-01 Fix over-enthusiastic masking of PPU jump instruction target addresses (historic bug)
2025-12-01 PPU: Fix size-1 spans not being rendered, and add a testcase that covers this
2025-12-03 Fix cosmetic lint issues
